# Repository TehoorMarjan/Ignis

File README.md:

# 🔥 Ignis Project - Ignis Lamp

An autonomous flame-shaped lamp/nightlight controlled by microcontroller with
WS2812B LED ring and **integrated Qi wireless charging**.

**Status** : Hardware validated ✅ - Firmware development in progress  
**Last update** : September 2025

## 🎯 Objectives

- **Autonomy** : 2-3 hours on LiPo battery (320 mAh)
- **LED Patterns** : Heartbeat, chase, fade, realistic flame effects
- **Control** : SW-18030 shock detector for interaction
- **Charging** : **Qi wireless** + automatic power-path management
- **Waterproof** : No USB port, induction charging only

## ⚡ IgnisV2 Electrical Architecture

```mermaid
flowchart TD
  QiCharger["📡 BQ51013B<br/>Qi Charger"] ==> Charger["🔌 BQ24073<br/>Battery Charger"]
  Charger <==> Battery["🔋 LiPo Battery<br/>320mAh"]
  Charger ==> Boost["⚡ FP6277 Boost<br/>3.7V → 5V"]

  subgraph SYS["System"]
    MCU["🖥️ ATtiny212 @ 20MHz"]
    ShockSensor["💥 SW-18030<br/>Shock Sensor"]
    MCU -. "User Interaction" .- ShockSensor
    MCU --> WS2812B["💡 WS2812B<br/>6 LEDs"]
  end

  Boost ==> SYS
  Charger -. "Charge Status" .-> MCU
  QiCharger -. "Coil Status" .-> MCU
```

## 📚 Documentation

This repository contains comprehensive documentation for all aspects of the
Ignis project. Navigate to the relevant sections based on your interests:

### 🎯 Project Management

- [📊 PROJECT_STATUS.md](PROJECT_STATUS.md) - Current project status,
  milestones, and development progress

### 💾 Firmware Development

- [🔧 firmware/README.md](firmware/README.md) - ATtiny212 firmware
  documentation, build instructions, and current implementation

### 🔌 Hardware Design

- [⚡ docs/calculations/electrical_design.md](docs/calculations/electrical_design.md) -
  Complete electrical calculations, component sizing, and power analysis
- [🔗 docs/references/schematics_references.md](docs/references/schematics_references.md) -
  Reference schematics and design patterns
- [📋 docs/datasheets/README.md](docs/datasheets/README.md) - Component
  datasheets and technical specifications

### 🎨 Mechanical Design

- [🖼️ mechanical/art/README.md](mechanical/art/README.md) - 3D artwork and
  Blender models (Flamme4 design)
- [🏗️ mechanical/cad/README.md](mechanical/cad/README.md) - CAD models,
  assemblies, and engineering drawings
- [🖨️ mechanical/stl/README.md](mechanical/stl/README.md) - 3D printable files
  and printing guidelines
- [📏 docs/calculations/filament.md](docs/calculations/filament.md) - 3D
  printing material calculations and optimization

---

**For Contributors**: Start with [PROJECT_STATUS.md](PROJECT_STATUS.md) to
understand current progress, then refer to the relevant documentation sections
above based on your area of contribution.

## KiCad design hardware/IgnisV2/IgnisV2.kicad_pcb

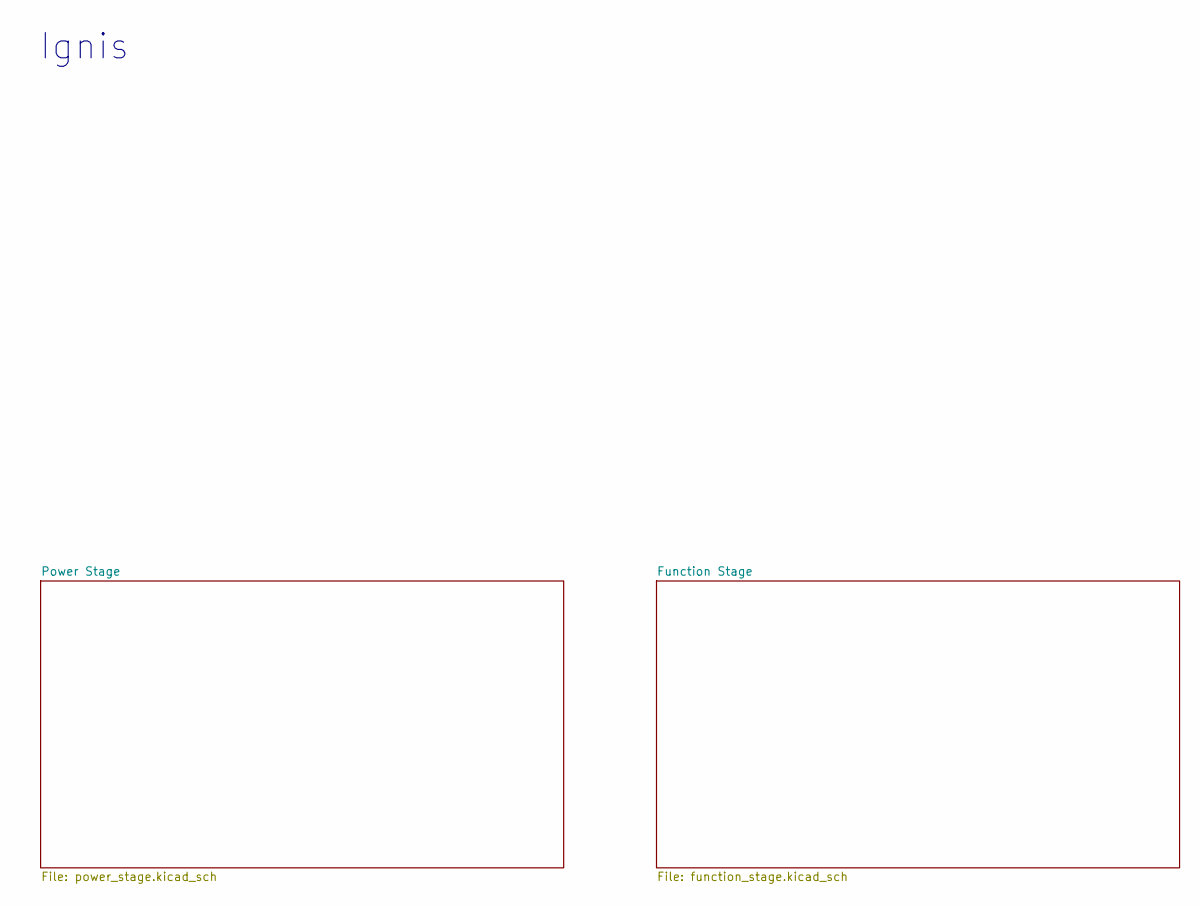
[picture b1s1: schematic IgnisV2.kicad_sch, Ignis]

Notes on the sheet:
Ignis

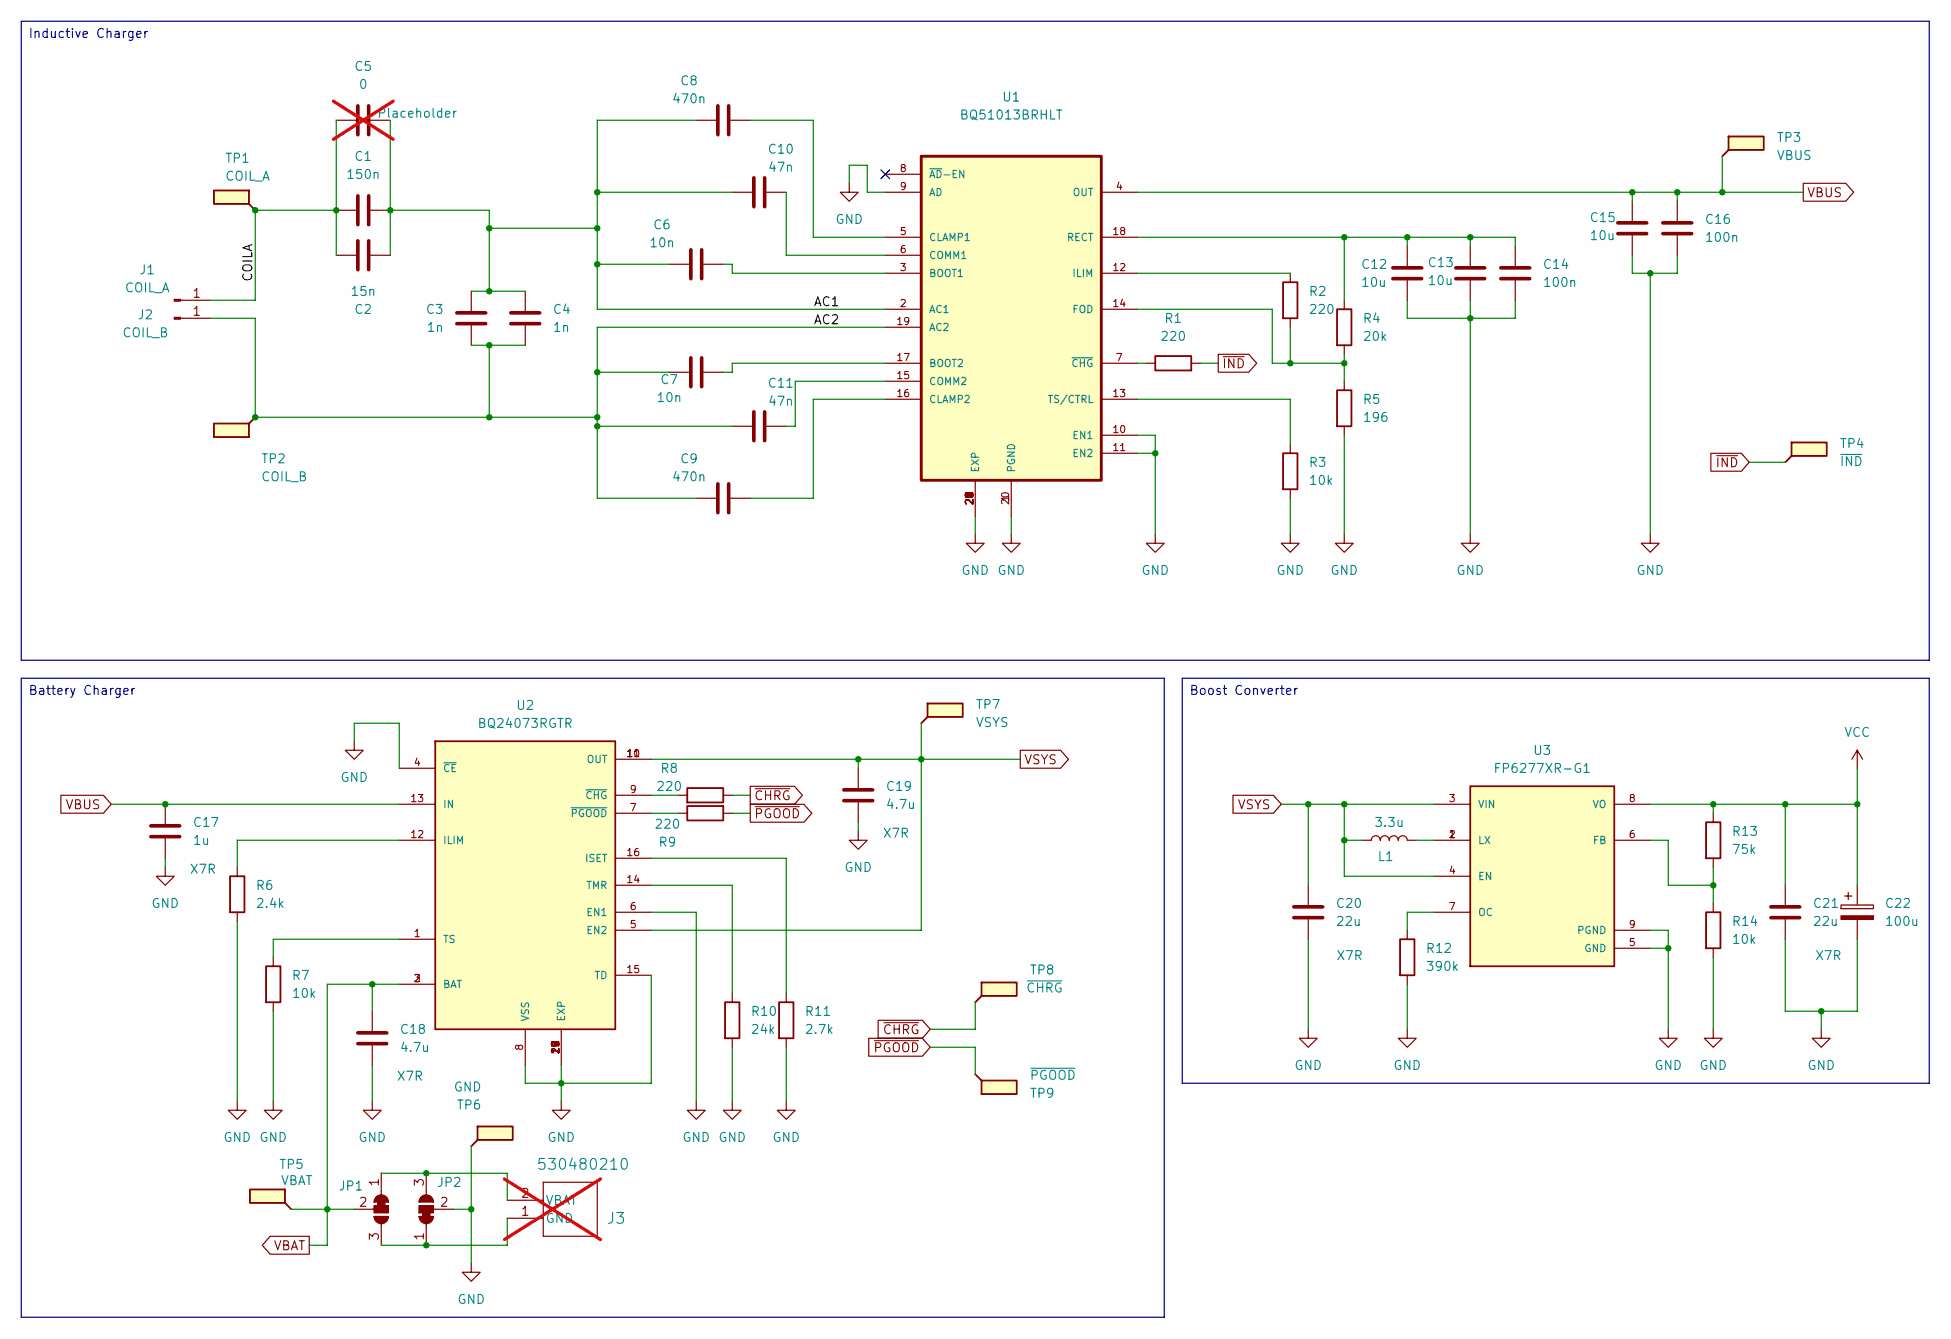
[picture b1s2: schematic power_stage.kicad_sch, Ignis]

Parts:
C1: 150n; C_0402_1005Metric; Voltage Rating 25V; LCSC C5448879
C2: 15n; C_0402_1005Metric; Voltage Rating 25V; LCSC C285020
C3, C4: 1n; C_0402_1005Metric; Voltage Rating 25V; LCSC C541372
C5: 0; C_0805_2012Metric_Pad1.18x1.45mm_HandSolder; Voltage Rating 25V; not fitted
C6, C7: 10n; C_0402_1005Metric; Voltage Rating 25V; LCSC C284987
C8, C9: 470n; C_0603_1608Metric; Voltage Rating 25V; LCSC C7503496
C10, C11: 47n; C_0402_1005Metric; Voltage Rating 25V; LCSC C5142571
C12, C13, C15: 10u; C_0402_1005Metric; Voltage Rating 16V; LCSC C7393849
C14, C16: 100n; C_0402_1005Metric; Voltage Rating 16V; LCSC C328914
C17: 1u; C_0603_1608Metric; Voltage Rating 16V; LCSC C76617
C18, C19: 4.7u; C_0603_1608Metric; Voltage Rating 16V; LCSC C22399629
C20, C21: 22u; C_1206_3216Metric; Voltage Rating 16V; LCSC C6119995
C22: 100u; CP_Elec_5x5.4; Voltage Rating 16V; LCSC C7461241
J1: COIL_A; TestPoint_THTPad_D1.5mm_Drill0.7mm
J2: COIL_B; TestPoint_THTPad_D1.5mm_Drill0.7mm
J3: 530480210; CONN02_530480210_MOL; not fitted
JP1: VBATS; SolderJumper-3_P1.3mm_Bridged12_RoundedPad1.0x1.5mm
JP2: VGNDS; SolderJumper-3_P1.3mm_Bridged12_RoundedPad1.0x1.5mm
L1: 3.3u; L_1008_2520Metric; LCSC C2049754
R1, R8, R9: 220; R_0402_1005Metric; LCSC C25091
R2: 220; R_0805_2012Metric; LCSC C17557
R3, R7, R14: 10k; R_0402_1005Metric; LCSC C25531
R4: 20k; R_0402_1005Metric; LCSC C25545
R5: 196; R_0805_2012Metric; LCSC C407413
R6: 2.4k; R_0402_1005Metric; LCSC C25882
R10: 24k; R_0402_1005Metric; LCSC C25549
R11: 2.7k; R_0402_1005Metric; LCSC C25885
R12: 390k; R_0402_1005Metric; LCSC C25557
R13: 75k; R_0402_1005Metric; LCSC C25570
TP1: COIL_A; TestPoint_Pad_D1.0mm
TP2: COIL_B; TestPoint_Pad_D1.0mm
TP3: VBUS; TestPoint_Pad_D1.0mm
TP4: ~{IND}; TestPoint_Pad_D1.0mm
TP5: VBAT; TestPoint_Pad_D1.0mm
TP6: GND; TestPoint_Pad_D1.0mm
TP7: VSYS; TestPoint_Pad_D1.0mm
TP8: ~{CHRG}; TestPoint_Pad_D1.0mm
TP9: ~{PGOOD}; TestPoint_Pad_D1.0mm
U1: BQ51013BRHLT; LCSC C2650154
U2: BQ24073RGTR; IC_BQ24073RGTR; LCSC C15220
U3: FP6277XR-G1; SOIC127P599X175-9N; PARTREV 0.65; LCSC C88312

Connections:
/Power Stage/AC1: C1.2, C2.2, C3.2, C4.2, C5.2, C6.1, C8.1, C10.1, U1.2 (AC1)
/Power Stage/AC2: C3.1, C4.1, C7.1, C9.1, C11.1, J2.1, TP2.1, U1.19 (AC2)
/Power Stage/COILA: C1.1, C2.1, C5.1, J1.1, TP1.1
GND: C12.2, C13.2, C14.2, C15.2, C16.2, C17.2, C18.2, C19.2, C20.2, C21.2, C22.2, JP2.2 (C), R3.2, R5.2, R6.2, R7.2, R10.2, R11.2, R12.2, R14.2, TP6.1, U1.1 (PGND), U1.9 (AD), U1.10 (EN1), U1.11 (EN2), U1.20 (PGND), U1.21 (EXP), U1.22 (EXP), U1.23 (EXP), U1.24 (EXP), U1.25 (EXP), U1.26 (EXP), U1.27 (EXP), U1.28 (EXP), U1.29 (EXP), U2.4 (~CE), U2.6 (EN1), U2.8 (VSS), U2.15 (TD), U2.17 (EXP), U2.18 (EXP), U2.19 (EXP), U2.20 (EXP), U2.21 (EXP), U2.22 (EXP), U3.5 (GND), U3.9 (PGND); also elsewhere on the board
unnamed: J3.1 (GND), JP1.3 (B), JP2.1 (A)
unnamed: J3.2 (VBAT), JP1.1 (A), JP2.3 (B)
unnamed: L1.2, U3.1 (LX), U3.2 (LX)
unnamed: C6.2, U1.3 (BOOT1)
unnamed: C7.2, U1.17 (BOOT2)
unnamed: C8.2, U1.5 (CLAMP1)
unnamed: C9.2, U1.16 (CLAMP2)
unnamed: C10.2, U1.6 (COMM1)
unnamed: C11.2, U1.15 (COMM2)
unnamed: R2.2, R4.2, R5.1, U1.14 (FOD)
unnamed: R2.1, U1.12 (ILIM)
unnamed: C12.1, C13.1, C14.1, R4.1, U1.18 (RECT)
unnamed: R3.1, U1.13 (TS/CTRL)
unnamed: R1.1, U1.7 (~CHG)
unnamed: R6.1, U2.12 (ILIM)
unnamed: R11.1, U2.16 (ISET)
unnamed: R10.1, U2.14 (TMR)
unnamed: R7.1, U2.1 (TS)
unnamed: R8.2, U2.9 (~CHG)
unnamed: R9.1, U2.7 (~PGOOD)
unnamed: R13.2, R14.1, U3.6 (FB)
unnamed: R12.1, U3.7 (OC)
VBAT: C18.1, JP1.2 (C), TP5.1, U2.2 (BAT), U2.3 (BAT)
VBUS: C15.1, C16.1, C17.1, TP3.1, U1.4 (OUT), U2.13 (IN)
VCC: C21.1, C22.1, R13.1, U3.8 (VO); also elsewhere on the board
VSYS: C19.1, C20.1, L1.1, TP7.1, U2.5 (EN2), U2.10 (OUT), U2.11 (OUT), U3.3 (VIN), U3.4 (EN); also elsewhere on the board
~CHRG: R8.1, TP8.1; also elsewhere on the board
~IND: R1.2, TP4.1; also elsewhere on the board
~PGOOD: R9.2, TP9.1; also elsewhere on the board

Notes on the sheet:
Inductive Charger
Battery Charger
Boost Converter

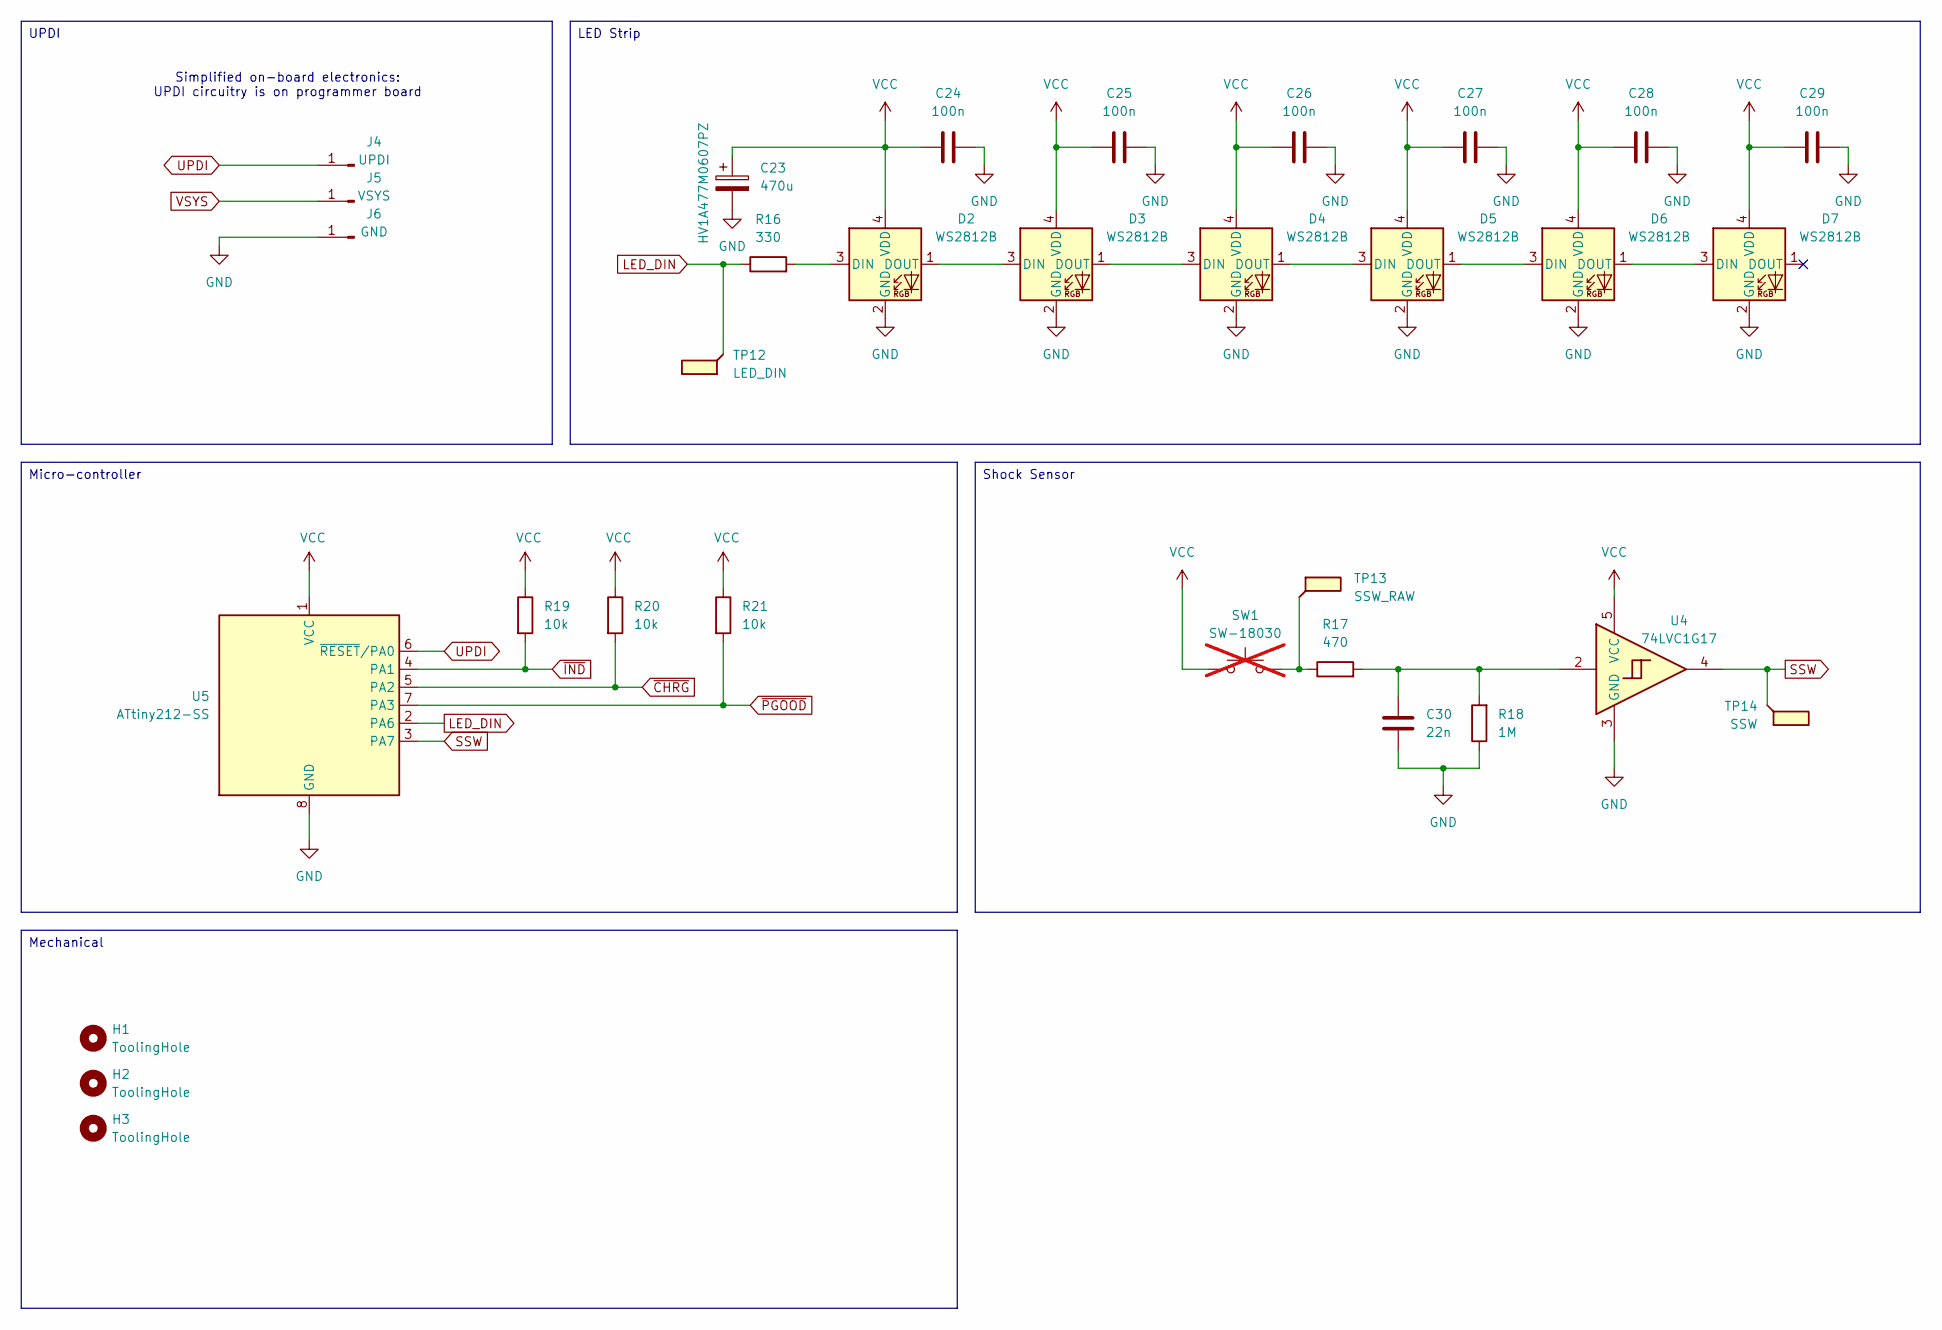
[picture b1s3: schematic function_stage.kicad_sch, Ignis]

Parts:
C23: 470u; CP_Elec_6.3x7.7; Voltage Rating 10V; LCSC C5246516
C24, C25, C26, C27, C28, C29: 100n; C_0402_1005Metric; LCSC C328914
C30: 22n; C_0402_1005Metric; LCSC C6266887
D2, D3, D4, D5, D6, D7: WS2812B; LED_WS2812B2020; LCSC C965555
H1, H2, H3: ToolingHole; ToolingHole_1.152mm
J4: UPDI; TestPoint_THTPad_D1.5mm_Drill0.7mm
J5: VSYS; TestPoint_THTPad_D1.5mm_Drill0.7mm
J6: GND; TestPoint_THTPad_D1.5mm_Drill0.7mm
R16: 330; R_0402_1005Metric; LCSC C12246
R17: 470; R_0402_1005Metric; LCSC C25167
R18: 1M; R_0402_1005Metric; LCSC C26087
R19, R20, R21: 10k; R_0402_1005Metric; LCSC C25531
SW1: SW-18030; SW-180; not fitted
TP12: LED_DIN; TestPoint_Pad_D1.0mm
TP13: SSW_RAW; TestPoint_Pad_D1.0mm
TP14: SSW; TestPoint_Pad_D1.0mm
U4: 74LVC1G17; IC_74LVC1G17GW_125; LCSC C426705
U5: ATtiny212-SS; SOIC-8_3.9x4.9mm_P1.27mm; LCSC C615533

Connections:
GND: C23.2, C24.2, C25.2, C26.2, C27.2, C28.2, C29.2, C30.2, D2.2 (GND), D3.2 (GND), D4.2 (GND), D5.2 (GND), D6.2 (GND), D7.2 (GND), J6.1, R18.1, U4.3 (GND), U5.8 (GND); also elsewhere on the board
LED_DIN: R16.1, TP12.1, U5.2 (PA6)
unnamed: C30.1, R17.2, R18.2, U4.2
unnamed: D2.3 (DIN), R16.2
unnamed: D2.1 (DOUT), D3.3 (DIN)
unnamed: D3.1 (DOUT), D4.3 (DIN)
unnamed: D4.1 (DOUT), D5.3 (DIN)
unnamed: D5.1 (DOUT), D6.3 (DIN)
unnamed: D6.1 (DOUT), D7.3 (DIN)
unnamed: R17.1, SW1.2, TP13.1
SSW: TP14.1, U4.4, U5.3 (PA7)
UPDI: J4.1, U5.6 (~RESET/PA0)
VCC: C23.1, C24.1, C25.1, C26.1, C27.1, C28.1, C29.1, D2.4 (VDD), D3.4 (VDD), D4.4 (VDD), D5.4 (VDD), D6.4 (VDD), D7.4 (VDD), R19.1, R20.1, R21.1, SW1.1, U4.5 (VCC), U5.1 (VCC); also elsewhere on the board
VSYS: J5.1; also elsewhere on the board
~CHRG: R20.2, U5.5 (PA2); also elsewhere on the board
~IND: R19.2, U5.4 (PA1); also elsewhere on the board
~PGOOD: R21.2, U5.7 (PA3); also elsewhere on the board

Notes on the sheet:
Simplified on-board electronics: UPDI circuitry is on programmer board
Shock Sensor
UPDI
Micro-controller
LED Strip
Mechanical

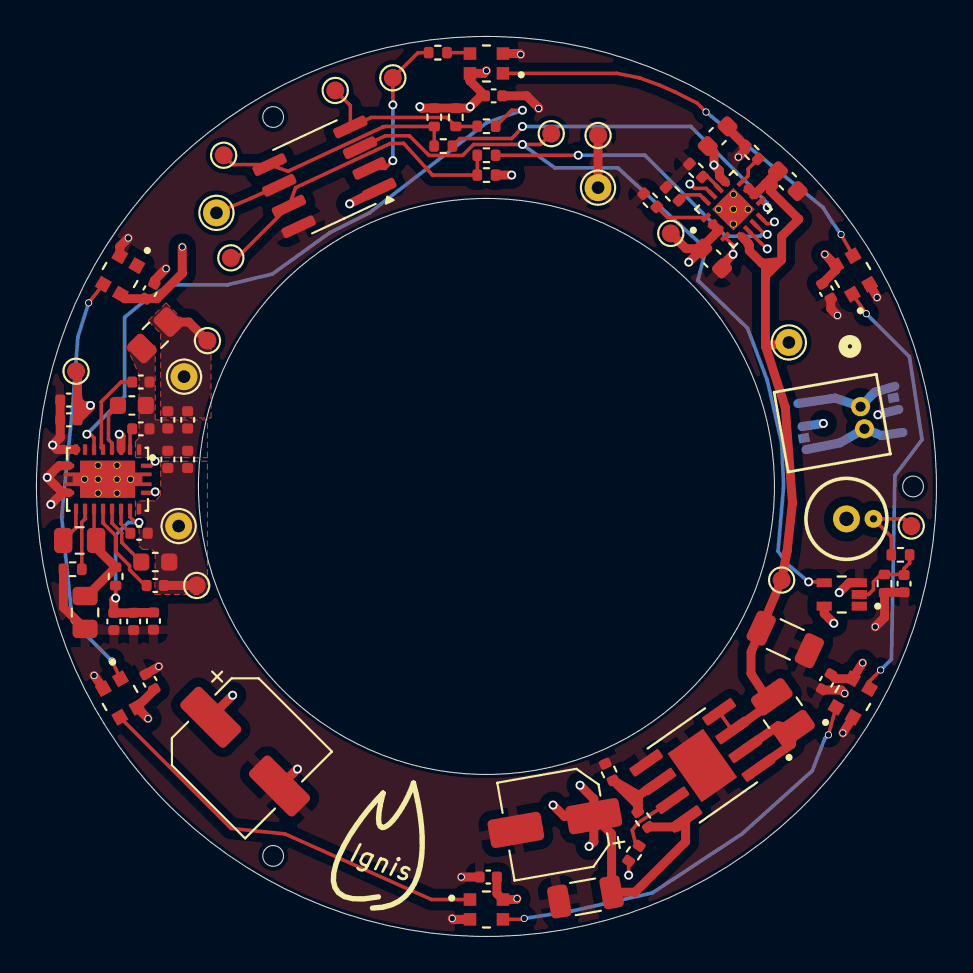
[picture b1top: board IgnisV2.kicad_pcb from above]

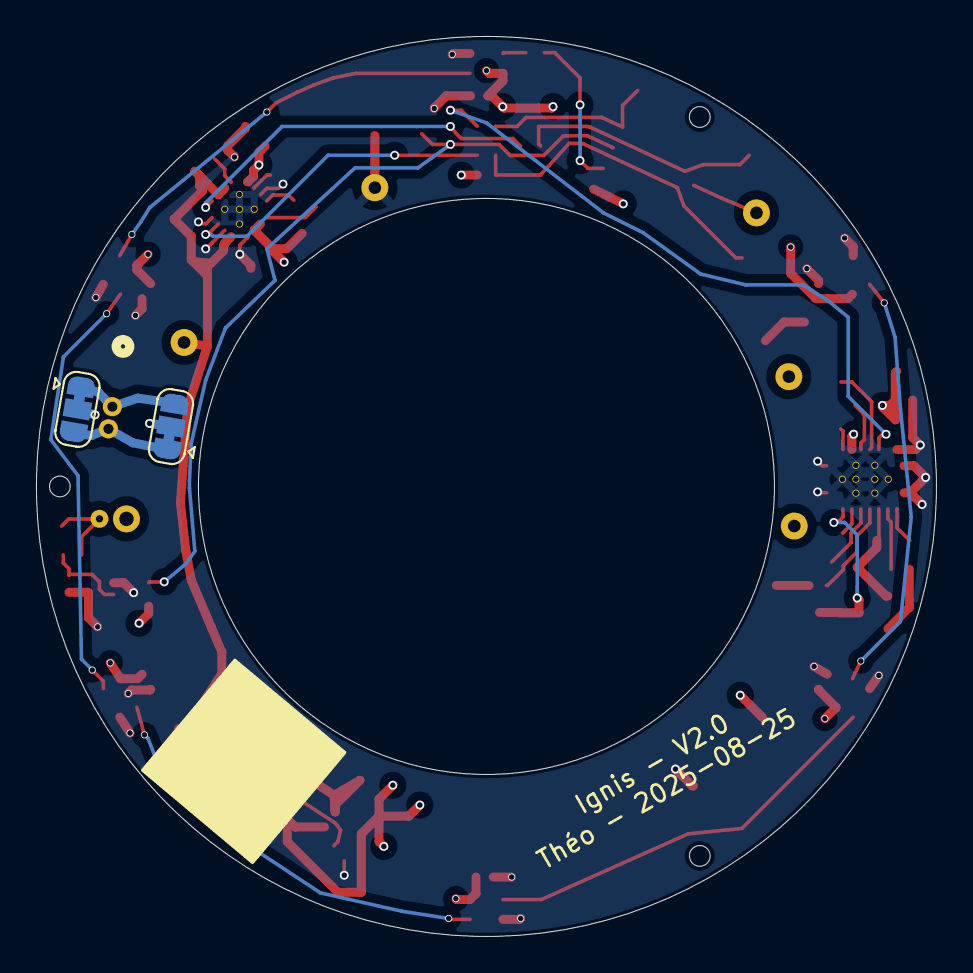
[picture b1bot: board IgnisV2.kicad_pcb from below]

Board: 4 copper layers, 50.0 x 50.0 mm, 86 parts (2 on the bottom side), 44 nets.

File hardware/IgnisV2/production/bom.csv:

Designator,Footprint,Quantity,Value,LCSC Part #
C1,0402,1,150n,C5448879
"C10, C11",0402,2,47n,C5142571
"C12, C13, C15",0402,3,10u,C7393849
"C14, C16, C24, C25, C26, C27, C28, C29",0402,8,100n,C328914
C17,0603,1,1u,C76617
"C18, C19",0603,2,4.7u,C22399629
C2,0402,1,15n,C285020
"C20, C21",1206,2,22u,C6119995
C22,CP_Elec_5x5.4,1,100u,C7461241
C23,CP_Elec_6.3x7.7,1,470u,C5246516
"C3, C4",0402,2,1n,C541372
C30,0402,1,22n,C6266887
C5,0805,1,0,
"C6, C7",0402,2,10n,C284987
"C8, C9",0603,2,470n,C7503496
"D2, D3, D4, D5, D6, D7",LED_WS2812B2020,6,WS2812B,C965555
L1,1008,1,3.3u,C2049754
"R1, R8, R9",0402,3,220,C25091
R10,0402,1,24k,C25549
R11,0402,1,2.7k,C25885
R12,0402,1,390k,C25557
R13,0402,1,75k,C25570
"R14, R19, R20, R21, R3, R7",0402,6,10k,C25531
R16,0402,1,330,C12246
R17,0402,1,470,C25167
R18,0402,1,1M,C26087
R2,0805,1,220,C17557
R4,0402,1,20k,C25545
R5,0805,1,196,C407413
R6,0402,1,2.4k,C25882
U1,BQ51013BRHLT,1,BQ51013BRHLT,C2650154
U2,IC_BQ24073RGTR,1,BQ24073RGTR,C15220
U3,SOIC127P599X175-9N,1,FP6277XR-G1,C88312
U4,IC_74LVC1G17GW_125,1,74LVC1G17,C426705
U5,SOIC-8_3.9x4.9mm_P1.27mm,1,ATtiny212-SS,C615533

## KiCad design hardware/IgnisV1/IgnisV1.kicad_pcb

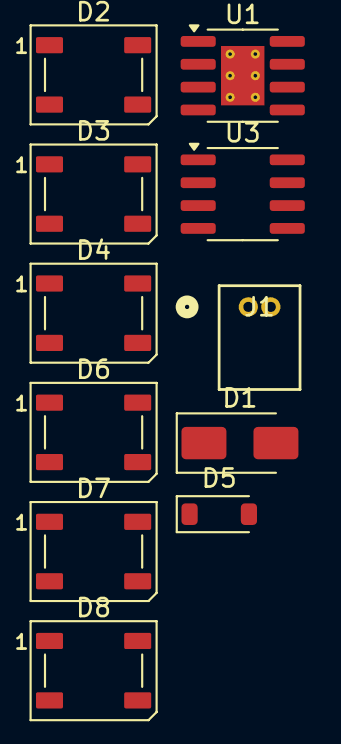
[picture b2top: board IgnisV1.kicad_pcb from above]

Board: 2 copper layers, 11 parts (0 on the bottom side), 10 nets, no tracks yet.

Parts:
D1: SS34; D_SMA
D2, D3, D4, D6, D7, D8: WS2812B; LED_WS2812B_PLCC4_5.0x5.0mm_P3.2mm
D5: LBAT46T1G; D_SOD-123
J1: 530480210; CONN02_530480210_MOL
U1: TP4056-42-ESOP8; SOIC-8-1EP_3.9x4.9mm_P1.27mm_EP2.41x3.3mm_ThermalVias
U3: ATtiny212-SS; SOIC-8_3.9x4.9mm_P1.27mm

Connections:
GND: D2.3 (VSS), D3.3 (VSS), D4.3 (VSS), D6.3 (VSS), D7.3 (VSS), D8.3 (VSS), J1.2, U1.1 (TEMP), U1.3 (GND), U1.9 (EPAD), U3.8 (GND)
LED_DIN: D2.4 (DIN), U3.2 (PA6)
unnamed: D2.2 (DOUT), D3.4 (DIN)
unnamed: D3.2 (DOUT), D4.4 (DIN)
unnamed: D4.2 (DOUT), D8.4 (DIN)
unnamed: D6.4 (DIN), D7.2 (DOUT)
unnamed: D7.4 (DIN), D8.2 (DOUT)
VBAT: J1.1, U1.5 (BAT)
VBUS: D1.2 (A), U1.4 (V_{CC}), U1.8 (CE)
VCC: D2.1 (VDD), D3.1 (VDD), D4.1 (VDD), D6.1 (VDD), D7.1 (VDD), D8.1 (VDD), U3.1 (VCC)

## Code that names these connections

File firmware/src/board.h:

/**
 * @file board.h
 * @brief Hardware abstraction layer for Ignis V2.2 PCB
 *
 * Project: Ignis - Autonomous flame-shaped lamp with wireless charging
 * Hardware: IgnisV2 PCB with ATtiny212, BQ24073, BQ51013B, WS2812B-2020
 * Version: V2.2
 *
 * This file contains board-specific definitions including pin assignments,
 * hardware configuration constants, and peripheral mappings for the
 * IgnisV2.2 PCB design.
 *
 * @author TheoToys
 * @date September 2025
 * @license MIT License - See LICENSE file for details
 */

#ifndef BOARD_H
#define BOARD_H

#include <Arduino.h>

// Board identification
#define BOARD_VERSION "IgnisV2.2"
#define BOARD_MCU "ATtiny212"

#define PIN_UPDI PIN_PA0    // UPDI programming pin
#define PIN_IND_B PIN_PA1   // Low when inductor receives power
#define PIN_CHRG_B PIN_PA2  // Low when battery is charging
#define PIN_PGOOD_B PIN_PA3 // Low when charging is complete
#define PIN_LED PIN_PA6     // WS2812B data pin
#define PIN_SSW PIN_PA7     // Shock detection switch pin

#define NUM_LEDS 6

#endif // BOARD_H

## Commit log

2025-08-15 🔥 Initial commit: Ignis flame lamp project setup
    ✅ Project structure & workspace configuration
    - VS Code workspace with PlatformIO integration
    - K&R code formatting configured (.clang-format)
    - Structured folders: firmware/, hardware/, mechanical/, docs/
    ✅ Firmware foundation (ATtiny212/412)
    - Working minimal firmware with button handling
2025-08-15 💡 Bootstrap using tinyNeoPixel for LED strip control
    - Add tinyNeoPixel library to handle LED strip
    - Configure led pins
2025-08-15 😠 Had to add firmware/.vscode/extensions.json because PlatformIO keeps recreating it in the wrong place
    - Check workspace file `Ignis.code-workspace` for real use
2025-08-15 🎨 Add initial and polished flame Blender models
    - Flamme1.blend: first version of simple flame shape
    - Flamme2.blend: refined flame with added eyes
2025-08-16 🧊 Finalize Blender models and exports
    - Restructure art/ directory with individual folders for each flame design
    - Add PNG previews and STL exports for both Flamme1 and Flamme2 models
    - Create dedicated stl/ directory with ready-to-print files filtered by Orca
    - Add comprehensive documentation for 3D models and printing guidelines
2025-08-17 🔺 Add low-poly flame models with PLA gradient materials
    - New low poly model derived from Flamme1.
    - Enhanced Blender workflow with automated screenshot export.
    - Updated material system to simulate PLA filament gradient (brown → yellow) for realistic 3D printing preview.
2025-08-17 🧹 Harmonisation docs : Lampe Ignis, conventions commit
    - Remplacement de "Flamme dans le sable" par "Lampe Ignis" partout
    - Ajout des règles d'emoji et de style pour les messages de commit
    - Clarification du concept du sable dans la documentation
2025-08-17 ✨ Experimental Flamme3 series with 4 variants and documentation
    - Exploring new Blender modeling techniques with advanced modifiers and sculpting.
    - Flamme3_4 stands out as the most refined model, with STL export ready for printing.
2025-08-17 📐 Corrected and updated electronic design calculations
    - Passives for TP4056
    - Passives for FP6277 Boost
    - Cleanup
2025-08-22 🔋 Implement BQ51013B inductive charging with TP4056 design
    - Implemented the BQ51013B for inductive recharge.
    - Implemented in the TP4056 design, but this will be abandonned to a BQ24073.
    - Added all needed components to Ignis library of symbols and footprints.
    - See calculations in `docs/calculations/electrical_design.md`
2025-08-23 ⚡ Rework LED strip and add shock switch filtering
    Includes rework of the LED strip
    Includes filter with schmidt trigger buffer to input shock switch SW18030
2025-08-23 🧩 Finalize IgnisV1-TP4056 schematics & add reference design
    - Finished schematics by adding necessary pull-ups on signal lines.
    - Copied electrical design from an older version for reference and traceability.
2025-08-23 💼 Add jobset to KiCAD project
    - Added IgnisV1-TP4056.kicad_jobset to the project for improved job management.
2025-08-24 🔧 Add complete SW-18030 component with KiCAD footprint and 3D model
    - Created missing KiCAD footprint for SW-18030 component
    - Designed 3D model in FreeCAD and exported as STEP format
    - Integrated STEP model into KiCAD library for 3D visualization
    - Downloaded component datasheet for reference documentation
2025-08-24 🧹 Clean up obsolete IgnisV1 PCB and update electrical design
    - Removed obsolete IgnisV1 PCB files (kicad_pcb, kicad_sch, etc.)
    - Replaced MCP73871 with BQ24073 charger IC throughout documentation
    - Updated BQ24073 component calculations (RISET, RTMR, RILIM)
    - Added comprehensive SW18030 shock sensor filter calculations
    - Updated thermal analysis for BQ24073 switching charger
    - Reorganized component sections and obsolete design history
2025-08-24 📝 Update commit message guidelines for clarity and consistency
    - Copilot Instructions
2025-08-24 🤩 Complete IgnisV2 PCB redesign with BQ24073 and improved manufacturability
    - Created new IgnisV2 KiCAD project with hierarchical schematic design
    - Migrated from MCP73871 to BQ24073 charger IC with proper footprint
    - Sourced all components from JLCPCB with verified availability and footprints
    - Removed on-board UPDI programming (moved to external programmer board)
    - Added comprehensive test points for debugging and validation
    - Implemented component placeholders for field tweaking without PCB respins
2025-08-25 🎨 Fix SW-18030 3D model colors for proper KiCAD STEP export
    - Updated FreeCAD model colors to export correctly in STEP format
    - Fixed KiCAD transparency issue where #000000 renders as transparent
    - Changed black surfaces to #010101 minimum to ensure visibility
    - Updated both STEP file and KiCAD footprint with corrected model
    Note: KiCAD treats exact #000000 color as transparent in STEP models.
    Use #010101 or darker grays for proper black appearance.
2025-08-25 🏭 Finalize IgnisV2 PCB design and prepare for JLCPCB production
    - Polished hierarchical schematics with clean signal routing
    - Completed full PCB layout with optimized component placement
    - Refined component selection for optimal JLCPCB compatibility
    - Generated production files (Gerbers, drill, BOM, pick&place) for fabrication
    - Exported 3D model snapshot for documentation and review
    - Added 74LVC1G17 datasheet for package selection reference
2025-08-26 🚨 Fix critical PCB issues caught during JLCPCB review
    - Fixed undersized vias (<0.3mm) in component footprints to avoid extra costs
    - Corrected WS2812B symbol pinout mismatch between standard and 2020 package
    - Updated WS2812B-2020 wiring to match proper pin assignments
    - Regenerated production files with corrected drill sizes and routing
    **Critical catch: WS2812B standard vs 2020 package have different pinouts!**
    Production halted and corrected before fabrication.
2025-08-29 🌊 Add official TheoToys logo assets
    - Added SVG and PNG versions of the TheoToys logo in various styles and sizes
    - Included LICENSE file for logo usage
    - Organized logo files for easy integration
2025-08-30 🎨 Complete logo cleanup and rebranding with new typography
    - Changed official logo font from Museo Rounded to "Dongle" Bold
    - Reorganized logo assets with consistent naming convention
    - Added Makefile for automated PNG export in multiple variants and sizes
    - Updated KiCAD worksheets for both IgnisV1 and IgnisV2 PCBs with new branding
    - Removed obsolete logo files and consolidated SVG sources
    - Exported updated schematic PDFs with refreshed corporate identity
2025-08-31 🔥 Add Flamme4 3D model with dual-wall design
    - Created new Blender model with improved flame geometry
    - Generated STL files for both outer shell and inner structure
    - Updated README with new model specifications and printing guidelines
2025-08-31 📐 Add mechanical visualization models for component assembly
    - Created BatteryPack.FCStd for visualizing battery placement in lamp assembly
    - Added Coil.FCStd to model power receiving coil positioning
    - Imported IgnisV2PCB.FCStd via KiCAD StepUp for PCB integration visualization
2025-08-31 📊 Add filament calculations for 3D printing optimization
    - Created filament.md with material usage estimates and printing parameters
    - Added calculations for mechanical components and prototyping costs
2025-08-31 🧹 Apply consistent formatting across documentation
    - Updated formatting in project documentation and README files
    - Standardized markdown structure and styling
    - Improved readability across technical specifications
2025-08-31 📝 Update documentation to reflect IgnisV2 production status
    - Updated PROJECT_STATUS.md and README.md for current hardware phase
2025-09-08 🔧 Reorganize CAD models and add IgnisV2.2 test stand
    - Reorganized CAD files into logical subdirectories (SW18030/, Misc/, TestStand/)
    - Added PNG previews for all mechanical components
    - Created custom TestStand for IgnisV2.2 PCB programming and validation
    - Generated STL files for 3D printing (Top, Bottom, Hook parts)
    - Added comprehensive README with component specifications and lessons learned
    - Documented TestStand V1 issues for future improvements
2025-09-08 🔮 Refactor firmware for IgnisV2.2 PCB and add UPDI support
    - Updated platformio.ini for proper UPDI programming with pymcuprog
    - Removed ATtiny412 support (PCBs now use ATtiny212 exclusively)
    - Created board.h for clean hardware abstraction layer
    - Refactored main.cpp as board testing program for validation
    - Updated README.md with accurate pin assignments and English translation
    - Added pymcuprog auto-installation script
2025-09-08 📚 Update project status and main README + translation
    - Translated README.md from French to English (other documents ongoing)
    - Cleaned up README.md
    - Updated PROJECT_STATUS.md and translated
    - Added Mermaid diagrams
2025-09-10 📸 Add real photo of TestStand V1 in action
    - Added IMG_20250910_213844.jpg showing 3D printed TestStand with IgnisV2.2 PCB
    - Updated README with actual usage documentation
2025-09-15 🧪 Add TestStand V2 with improved design and pogo pin support
    - Created TestStandV2 addressing V1 issues (hook attachment, cable management)
    - Added proper pogo pin support for both test pads and drilled holes
    - Designed Guide/Base system with PCB alignment sticks
    - Generated complete STL set and 3MF file for 3D printing
    - Added IgnisV2TP.csv mapping test pads to connector positions and cable colors
    - Included real photos showing TestStand V2 in action with IgnisV2.2 PCB
2025-09-16 📦 Add UPDI Flasher Box CAD model and documentation
    - Created FreeCAD model for UPDI programmer enclosure
    - Added STL files for 3D printing (Top and Bottom parts)
    - Updated mechanical CAD README with complete section
    - Includes protoboard-based UPDI circuit with power selection
2025-09-17 ⚙️ Fix UPDI Flasher Box mechanical dimensions
    - Corrected threaded insert holes diameter (were too wide)
    - Fixed switch slot position and alignment
    - Updated FreeCAD model and exported STL files
2025-09-22 🔍 Document inductive charging failure and troubleshooting
    - Added comprehensive analysis of IgnisV2.2 Qi charging issues
2025-10-06 ⚡ Add comprehensive UPDI programmer documentation
    - Created detailed README with circuit schematics and pinouts
    - Added Fritzing breadboard design and assembled photo
    - Documented EPLZON protoboard specifications and assembly
    - Included enclosure reference and usage instructions
2025-11-19 🉑 Translate electrical design to english and doc cosmetics
